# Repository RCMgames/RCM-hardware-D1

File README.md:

# RCM-hardware-D1

v1.0

* 1.75 by 1.575 inches, 44.45 by 40.0 millimeters
* 2 motors (one L293D)
* 2 servos OR qwiic connector
* Qwiic-Compatible
* runs on 4 NiMH AAs
* battery monitoring
* uses a Wemos D1 mini with esp8266 CPU

The goal of this project is to make the cheapest [RCM board](https://github.com/rcmgames).

Program with [RCMv2](https://github.com/rcmgames/rcmv2)

The RCM D1 uses a Wemos D1 mini v4.0.0 esp8266 board. 

Use the AVR versions of JMotor functions not the ESP32 versions.

## Options for purchasing

* [PCBWay link](https://www.pcbway.com/project/shareproject/Cheap_wifi_connected_Robot_Control_Module_RCM_D1_v1_0_a19b71a2.html)
* send the gerbers to a PCB manufacturer of your choice

## Components
Solder by hand to assemble your boards.
| part | links | quantity | notes |
| ----- | ----- | ----- | ----- |
| RCM D1 circuit board | see options for purchasing above | 1 | |
| Wemos D1 mini with esp8266 | [link](https://www.wemos.cc/en/latest/d1/d1_mini.html) | 1 | |
| L293D | [digikey](https://www.digikey.com/en/products/detail/texas-instruments/L293DNE/379724) | 1 | |
| 16 pin IC socket | | 1 | optional |
| 18k resistor | [digikey](https://www.digikey.com/en/products/detail/stackpole-electronics-inc/RNMF14FTC18K0/2617300) | 1 | R1 |
| 10k resistor | [digikey](https://www.digikey.com/en/products/detail/yageo/MFR-12FTF52-10K/9133815) | 1 | R2 |
| 47uF capacitor | [digikey](https://www.digikey.com/en/products/detail/rubycon/63ZLJ47M6-3X11/3134467) | 1 | |
| Qwiic connector (JST SH) | [digikey](https://www.digikey.com/en/products/detail/jst-sales-america-inc/SM04B-SRSS-TB/926710) | 1 | optional, for qwiic connector |
| 2x3 male header pins | | 1 | for servos |
| 2 female header pins | | 2 | for motors |
| 8 female header pins | | 2 | often included with the wemos D1 |
| 8 male header pins | | 2 | often included with the wemos D1 |
| battery wires | [JST RCY](https://www.amazon.com/dp/B00Z04QFN2/) or battery plug of your choice | 1 | |

## Acknowledgements

The RCM D1 was originally created for [PNW Assistive Technology's RC car project](https://github.com/PNW-AT/rc-car-car)

Thanks for the WemosD1 Kicad footprints! https://github.com/rubienr/wemos-d1-mini-kicad

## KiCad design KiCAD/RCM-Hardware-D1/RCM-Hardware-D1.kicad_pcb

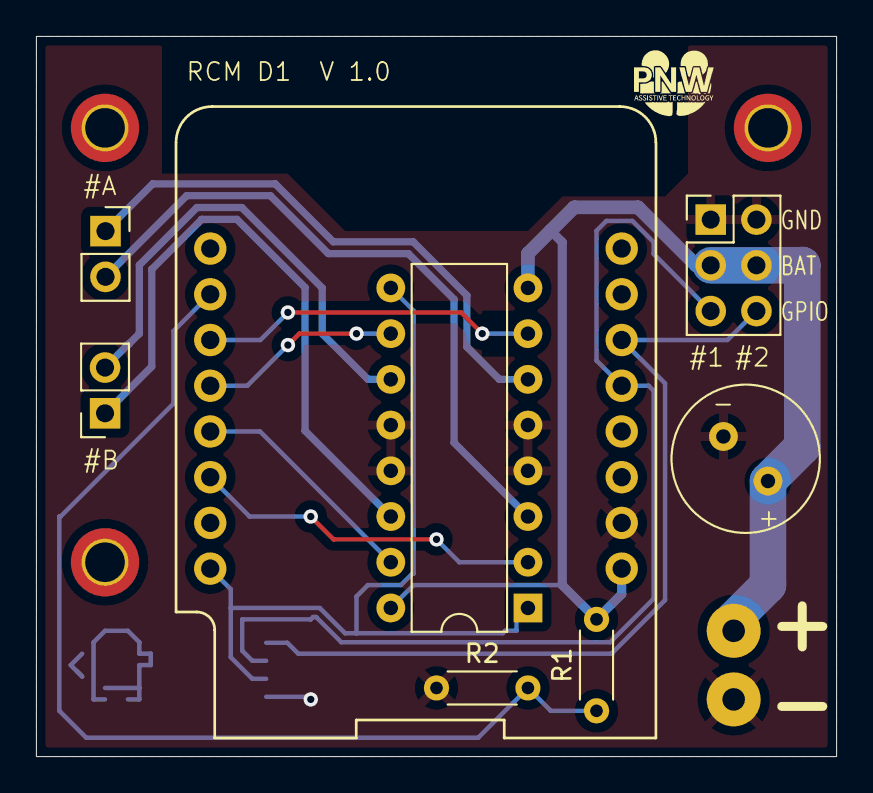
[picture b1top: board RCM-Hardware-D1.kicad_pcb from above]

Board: 2 copper layers, 44.4 x 40.0 mm, 10 parts (1 on the bottom side), 14 nets.

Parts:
C1: C_Polarized; C_Radial_D8.0mm_H11.5mm_P3.50mm
J1, J2: Conn_01x02_Pin; PinSocket_1x02_P2.54mm_Vertical
J3: battery; battery wires
J6: Conn_01x04_Pin; JST_SH_SM04B-SRSS-TB_1x04-1MP_P1.00mm_Horizontal
J7: Conn_01x06_Pin; PinHeader_2x03_P2.54mm_Vertical
R1, R2: R; R_Axial_DIN0204_L3.6mm_D1.6mm_P5.08mm_Horizontal
U1: WeMos_D1_mini; wemos-d1-mini-with-pin-header
U2: L293D; DIP-16_W7.62mm

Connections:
+3.3V: J6.2, U1.8 (3.3V), U2.1 (EN1,2), U2.9 (EN3,4)
GND: C1.2, J3.2, J6.1, J7.1, J7.2, R2.1, U1.10 (GND), U2.4 (GND), U2.5 (GND), U2.12 (GND), U2.13 (GND)
unnamed: J1.1, U2.14 (4Y)
unnamed: J1.2, U2.11 (3Y)
unnamed: J2.1, U2.6 (2Y)
unnamed: J2.2, U2.3 (1Y)
unnamed: C1.1, J3.1, J7.3, J7.4, R1.2, U1.9 (5V), U2.8 (VCC2), U2.16 (VCC1)
unnamed: J6.3, J7.5, U1.13 (D2)
unnamed: J6.4, J7.6, U1.14 (D1)
unnamed: R1.1, R2.2, U1.2 (A0)
unnamed: U1.3 (D0), U2.7 (2A)
unnamed: U1.4 (D5), U2.10 (3A)
unnamed: U1.5 (D6), U2.15 (4A)
unnamed: U1.6 (D7), U2.2 (1A)

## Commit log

2024-06-03 initial KiCAD commit
2024-06-04 set up kicad
2024-06-04 update kicad
2024-07-19 Continued the KeyCAD for the circuit board
2024-07-19 finished the KiCAD and created Gerbers
2024-07-19 add screenshots
2024-07-26 Update README.md with component list
2024-07-30 add photos
